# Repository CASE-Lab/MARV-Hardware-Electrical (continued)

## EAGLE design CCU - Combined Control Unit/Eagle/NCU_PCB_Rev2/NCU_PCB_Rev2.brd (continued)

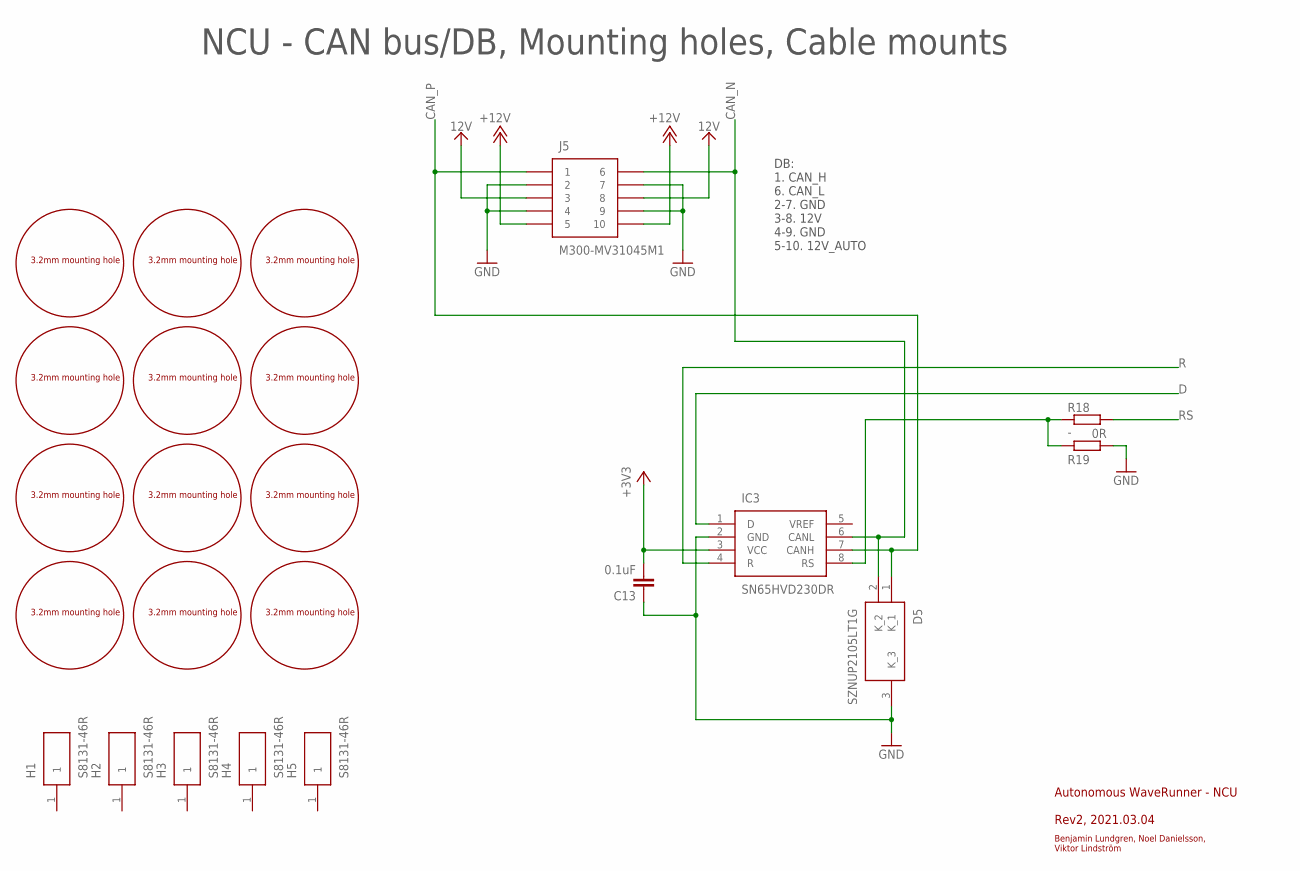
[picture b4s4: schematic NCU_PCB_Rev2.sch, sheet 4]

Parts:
C13: 0.1uF; C0603
D5: SZNUP2105LT1G; SOT96P237X111-3N
H1, H2, H3, H4, H5: S8131-46R; S813146R
HOLE5, HOLE6, HOLE7, HOLE8, HOLE9, HOLE10, HOLE11, HOLE12, HOLE13, HOLE14, HOLE15, HOLE16: M3_MOUNTING_HOLE
IC3: SN65HVD230DR; SOT127P600X175-8N
J5: M300-MV31045M1; M300MV31045M1
R18: -; R0603
R19: 0R; R0603

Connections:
12V: J5.3, J5.8; also elsewhere on the board
+3V3: C13.2, IC3.3 (VCC); also elsewhere on the board
+12V: J5.5, J5.10; also elsewhere on the board
CAN_N: D5.2 (K_2), IC3.6 (CANL), J5.6
CAN_P: D5.1 (K_1), IC3.7 (CANH), J5.1
D: IC3.1 (D); also elsewhere on the board
GND: C13.1, D5.3 (K_3), IC3.2 (GND), J5.2, J5.4, J5.7, J5.9, R19.1; also elsewhere on the board
unnamed: IC3.8 (RS), R18.1, R19.2
R: IC3.4 (R); also elsewhere on the board
RS: R18.2; also elsewhere on the board

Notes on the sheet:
Benjamin Lundgren, Noel Danielsson, Viktor Lindström
NCU - CAN bus/DB, Mounting holes, Cable mounts
DB: 1. CAN_H 6. CAN_L 2-7. GND 3-8. 12V 4-9. GND 5-10. 12V_AUTO
Autonomous WaveRunner - NCU
Rev2, 2021.03.04

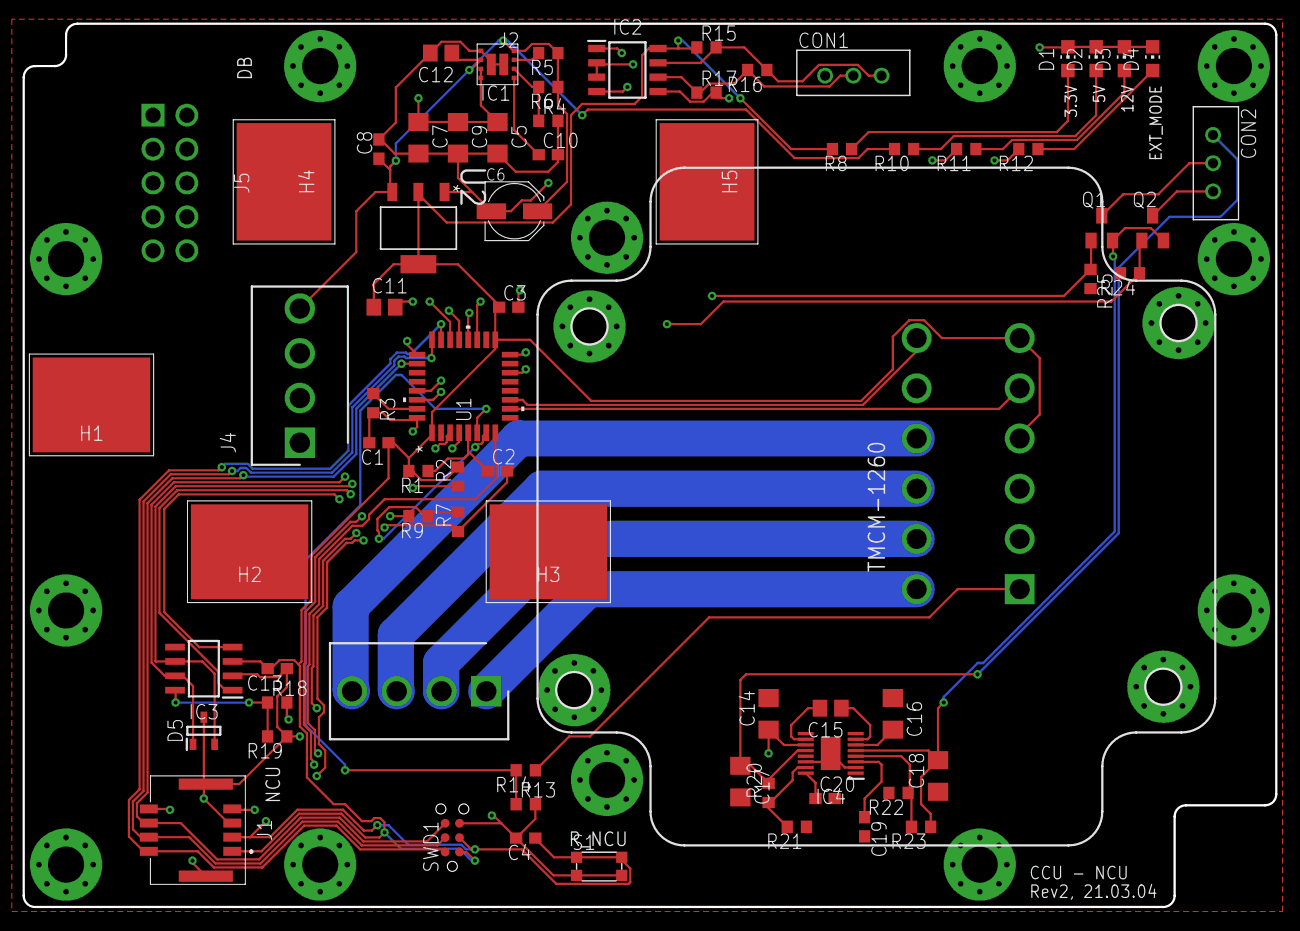
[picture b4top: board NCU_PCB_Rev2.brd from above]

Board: 4 copper layers, 110.9 x 78.2 mm, 89 parts (1 on the bottom side), 53 nets.

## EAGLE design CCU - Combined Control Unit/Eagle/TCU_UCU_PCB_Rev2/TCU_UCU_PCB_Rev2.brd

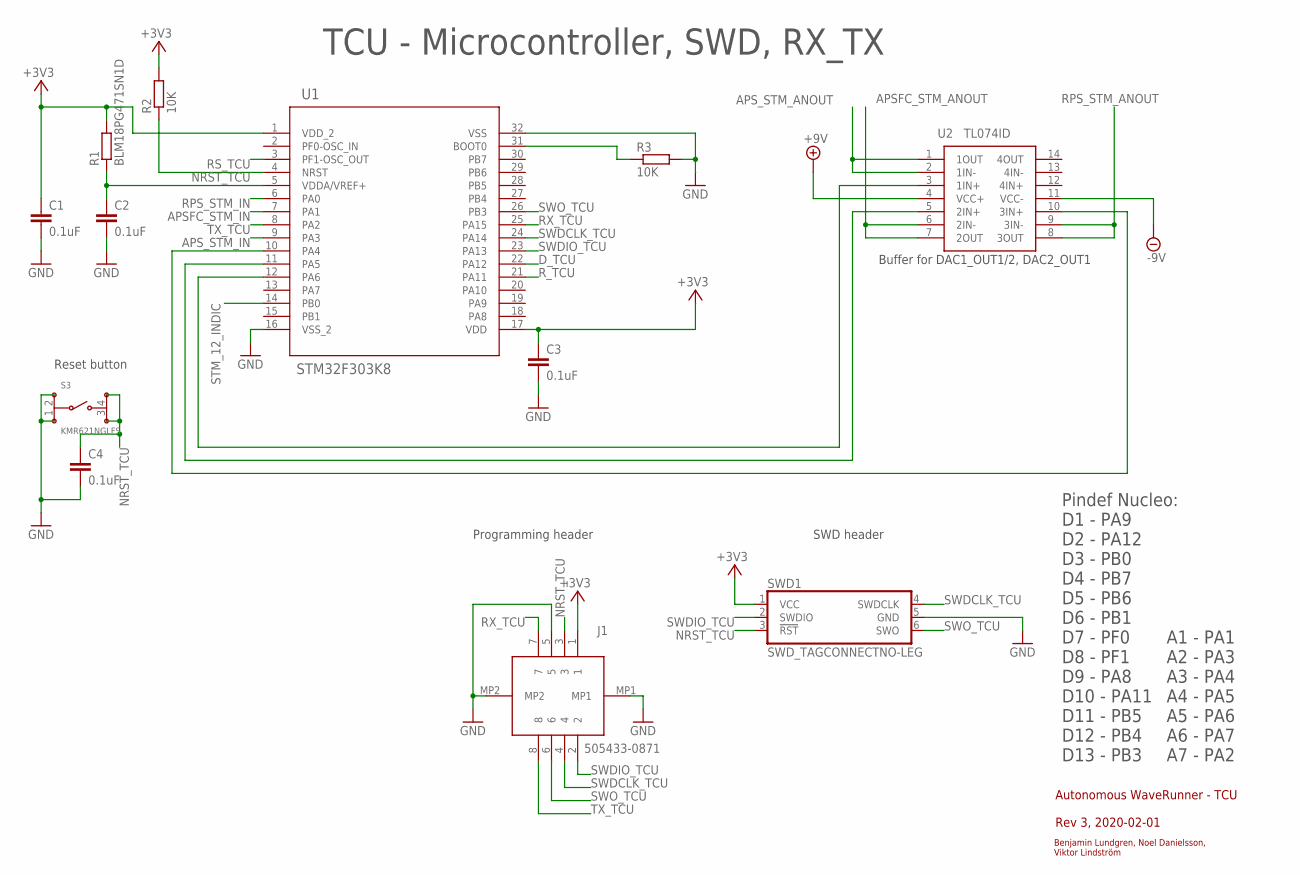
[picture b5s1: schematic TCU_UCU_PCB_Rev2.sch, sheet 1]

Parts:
C1, C2, C3, C4: 0.1uF; C0603
J1: 505433-0871; 5054330871
R1: BLM18PG471SN1D; R0603
R2, R3: 10K; R0603
S3: KMR621NGLFS
SWD1: SWD_TAGCONNECTNO-LEG; TC2030-IDC-NL
U1: STM32F303K8; LQFP-32
U2: TL074ID; SOIC127P600X175-14N

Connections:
+3V3: C1.1, C3.1, J1.1, R1.2, R2.2, SWD1.1 (VCC), U1.1 (VDD_2), U1.17 (VDD); also elsewhere on the board
+9V: U2.4 (VCC+); also elsewhere on the board
-9V: U2.11 (VCC-); also elsewhere on the board
APSFC_STM_ANOUT: U2.6 (2IN-), U2.7 (2OUT); also elsewhere on the board
APSFC_STM_IN: U1.7 (PA1); also elsewhere on the board
APS_STM_ANOUT: U2.1 (1OUT), U2.2 (1IN-); also elsewhere on the board
APS_STM_IN: U1.9 (PA3); also elsewhere on the board
D_TCU: U1.22 (PA12); also elsewhere on the board
GND: C1.2, C2.2, C3.2, C4.2, J1.5, J1.MP1, J1.MP2, R3.2, S3.1, S3.2, SWD1.5 (GND), U1.16 (VSS_2), U1.32 (VSS); also elsewhere on the board
unnamed: U1.11 (PA5), U2.5 (2IN+)
unnamed: U1.12 (PA6), U2.3 (1IN+)
unnamed: U1.10 (PA4), U2.10 (3IN+)
unnamed: C2.1, R1.1, U1.5 (VDDA/VREF+)
unnamed: R3.1, U1.31 (BOOT0)
NRST_TCU: C4.1, J1.3, R2.1, S3.3, S3.4, SWD1.3 (!RST), U1.4 (NRST)
RPS_STM_ANOUT: U2.8 (3OUT), U2.9 (3IN-); also elsewhere on the board
RPS_STM_IN: U1.6 (PA0); also elsewhere on the board
RS_TCU: U1.3 (PF1-OSC_OUT); also elsewhere on the board
RX_TCU: J1.7, U1.25 (PA15)
R_TCU: U1.21 (PA11); also elsewhere on the board
STM_12_INDIC: U1.14 (PB0); also elsewhere on the board
SWDCLK_TCU: J1.4, SWD1.4 (SWDCLK), U1.24 (PA14)
SWDIO_TCU: J1.2, SWD1.2 (SWDIO), U1.23 (PA13)
SWO_TCU: J1.6, SWD1.6 (SWO), U1.26 (PB3)
TX_TCU: J1.8, U1.8 (PA2)

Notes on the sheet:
Autonomous WaveRunner - TCU
Rev 3, 2020-02-01
Benjamin Lundgren, Noel Danielsson, Viktor Lindström
Buffer for DAC1_OUT1/2, DAC2_OUT1
Pindef Nucleo: D1 - PA9 D2 - PA12 D3 - PB0 D4 - PB7 D5 - PB6 D6 - PB1 D7 - PF0 D8 - PF1 D9 - PA8 D10 - PA11 D11 - PB5 D12 - PB4 D13 - PB3
A1 - PA1 A2 - PA3 A3 - PA4 A4 - PA5 A5 - PA6 A6 - PA7 A7 - PA2
TCU - Microcontroller, SWD, RX_TX
Programming header
SWD header
Reset button

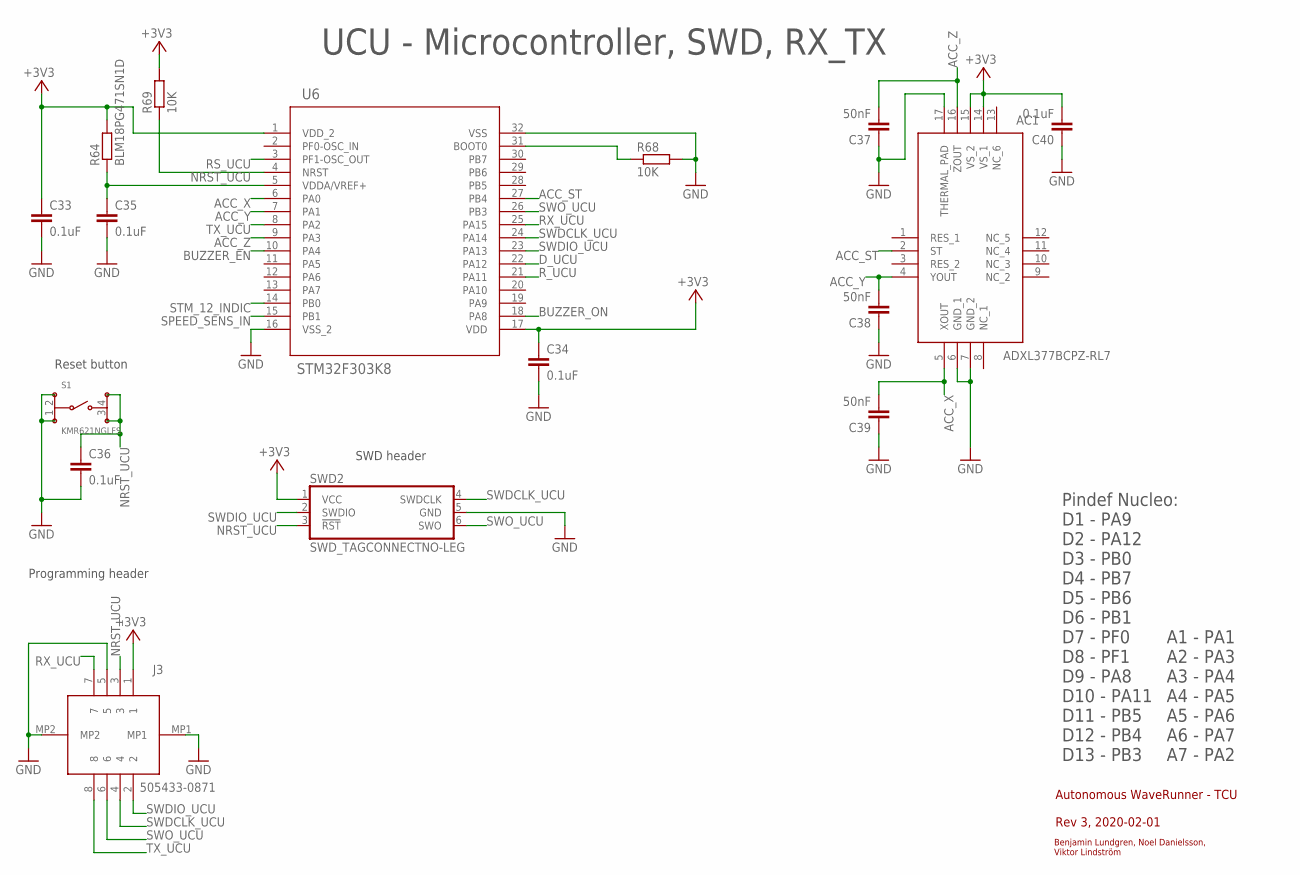
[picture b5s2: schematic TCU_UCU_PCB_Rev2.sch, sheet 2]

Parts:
AC1: ADXL377BCPZ-RL7; QFN50P300X300X150-17N
C33, C34, C35, C36, C40: 0.1uF; C0603
C37, C38, C39: 50nF; C0603
J3: 505433-0871; 5054330871
R64: BLM18PG471SN1D; R0603
R68, R69: 10K; R0603
S1: KMR621NGLFS
SWD2: SWD_TAGCONNECTNO-LEG; TC2030-IDC-NL
U6: STM32F303K8; LQFP-32

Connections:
+3V3: AC1.14 (VS_1), AC1.15 (VS_2), C33.1, C34.1, C40.2, J3.1, R64.2, R69.2, SWD2.1 (VCC), U6.1 (VDD_2), U6.17 (VDD); also elsewhere on the board
ACC_ST: AC1.2 (ST), U6.27 (PB4)
ACC_X: AC1.5 (XOUT), C39.2, U6.6 (PA0)
ACC_Y: AC1.4 (YOUT), C38.2, U6.7 (PA1)
ACC_Z: AC1.16 (ZOUT), C37.2, U6.9 (PA3)
BUZZER_EN: U6.10 (PA4); also elsewhere on the board
BUZZER_ON: U6.18 (PA8); also elsewhere on the board
D_UCU: U6.22 (PA12); also elsewhere on the board
GND: AC1.6 (GND_1), AC1.7 (GND_2), AC1.17 (THERMAL_PAD), C33.2, C34.2, C35.2, C36.2, C37.1, C38.1, C39.1, C40.1, J3.5, J3.MP1, J3.MP2, R68.2, S1.1, S1.2, SWD2.5 (GND), U6.16 (VSS_2), U6.32 (VSS); also elsewhere on the board
unnamed: C35.1, R64.1, U6.5 (VDDA/VREF+)
unnamed: R68.1, U6.31 (BOOT0)
NRST_UCU: C36.1, J3.3, R69.1, S1.3, S1.4, SWD2.3 (!RST), U6.4 (NRST)
RS_UCU: U6.3 (PF1-OSC_OUT); also elsewhere on the board
RX_UCU: J3.7, U6.25 (PA15)
R_UCU: U6.21 (PA11); also elsewhere on the board
SPEED_SENS_IN: U6.15 (PB1); also elsewhere on the board
STM_12_INDIC: U6.14 (PB0); also elsewhere on the board
SWDCLK_UCU: J3.4, SWD2.4 (SWDCLK), U6.24 (PA14)
SWDIO_UCU: J3.2, SWD2.2 (SWDIO), U6.23 (PA13)
SWO_UCU: J3.6, SWD2.6 (SWO), U6.26 (PB3)
TX_UCU: J3.8, U6.8 (PA2)

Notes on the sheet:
Autonomous WaveRunner - TCU
Rev 3, 2020-02-01
Benjamin Lundgren, Noel Danielsson, Viktor Lindström
UCU - Microcontroller, SWD, RX_TX
Programming header
SWD header
Reset button
Pindef Nucleo: D1 - PA9 D2 - PA12 D3 - PB0 D4 - PB7 D5 - PB6 D6 - PB1 D7 - PF0 D8 - PF1 D9 - PA8 D10 - PA11 D11 - PB5 D12 - PB4 D13 - PB3
A1 - PA1 A2 - PA3 A3 - PA4 A4 - PA5 A5 - PA6 A6 - PA7 A7 - PA2

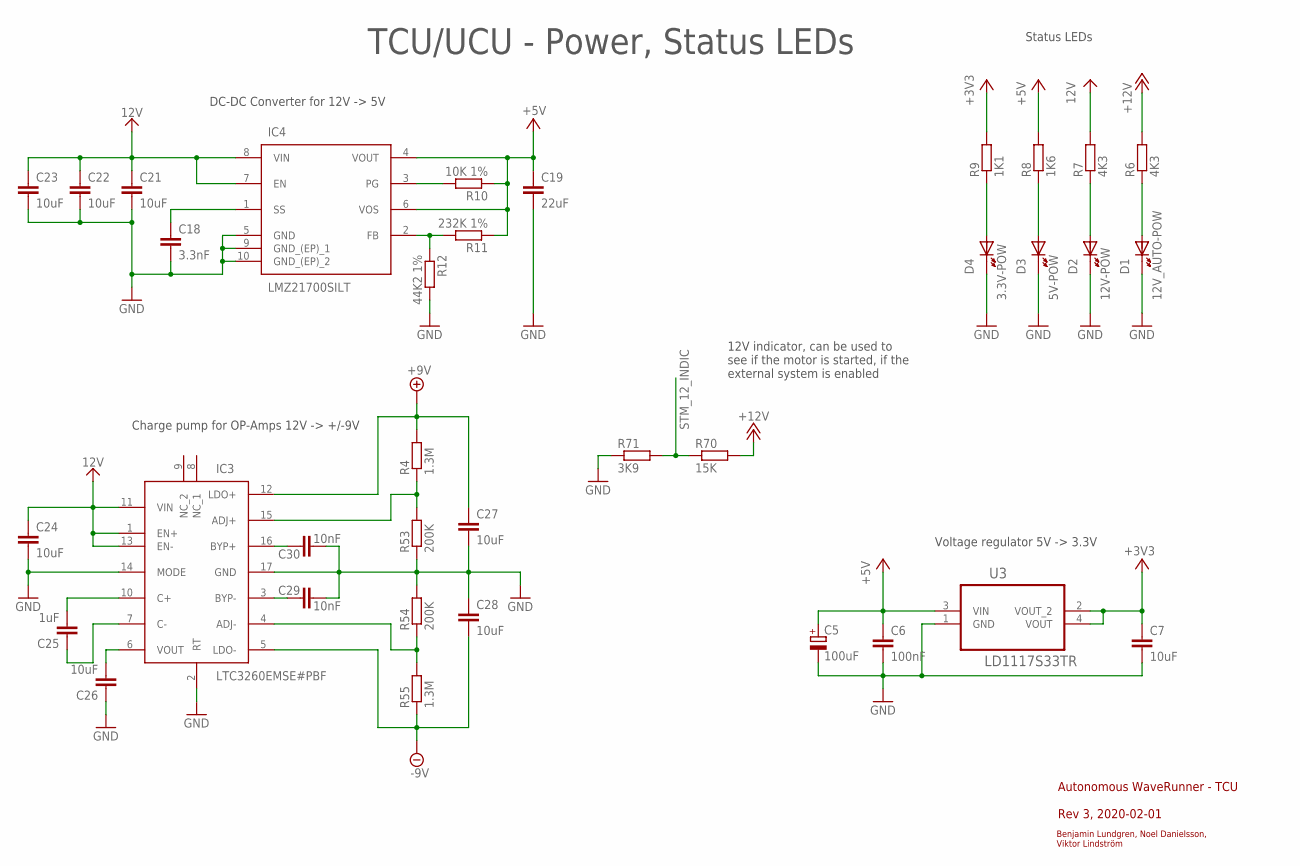
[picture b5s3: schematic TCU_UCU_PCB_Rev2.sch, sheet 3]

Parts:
C5: 100uF; PANASONIC_C
C6: 100nF; C0603
C7: 10uF; C0805
C18: 3.3nF; C0603
C19: 22uF; C0805
C21, C22, C23, C24, C26, C27, C28: 10uF; C1206
C25: 1uF; C0805
C29, C30: 10nF; C0603
D1: 12V_AUTO-POW; CHIP-LED0805
D2: 12V-POW; CHIP-LED0805
D3: 5V-POW; CHIP-LED0805
D4: 3.3V-POW; CHIP-LED0805
IC3: LTC3260EMSE#PBF; SOP50P490X110-17N
IC4: LMZ21700SILT; SIL0008E
R4, R55: 1.3M; R0603
R6, R7: 4K3; R0603
R8: 1K6; R0603
R9: 1K1; R0603
R10: 10K 1%; R0603
R11: 232K 1%; R0603
R12: 44K2 1%; R0603
R53, R54: 200K; R0603
R70: 15K; R0603
R71: 3K9; R0603
U3: LD1117S33TR; SOT230P700X180-4N

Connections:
12V: C21.1, C22.1, C23.1, C24.1, IC3.1 (EN+), IC3.11 (VIN), IC3.13 (EN-), IC4.7 (EN), IC4.8 (VIN), R7.2; also elsewhere on the board
+3V3: C7.1, R9.2, U3.2 (VOUT_2), U3.4 (VOUT); also elsewhere on the board
+5V: C5.+, C6.1, C19.1, IC4.4 (VOUT), IC4.6 (VOS), R8.2, R10.1, R11.1, U3.3 (VIN); also elsewhere on the board
+9V: C27.1, IC3.12 (LDO+), R4.2; also elsewhere on the board
+12V: R6.2, R70.2; also elsewhere on the board
-9V: C28.2, IC3.5 (LDO-), R55.1; also elsewhere on the board
GND: C5.-, C6.2, C7.2, C18.2, C19.2, C21.2, C22.2, C23.2, C24.2, C26.1, C27.2, C28.1, C29.2, C30.2, D1.C (K), D2.C (K), D3.C (K), D4.C (K), IC3.2 (RT), IC3.14 (MODE), IC3.17 (GND), IC4.5 (GND), IC4.9 (GND_(EP)_1), IC4.10 (GND_(EP)_2), R12.2, R53.1, R54.2, R71.1, U3.1 (GND); also elsewhere on the board
unnamed: C25.2, IC3.10 (C+)
unnamed: D1.A, R6.1
unnamed: IC4.2 (FB), R11.2, R12.1
unnamed: C18.1, IC4.1 (SS)
unnamed: D2.A, R7.1
unnamed: IC4.3 (PG), R10.2
unnamed: C25.1, IC3.7 (C-)
unnamed: C26.2, IC3.6 (VOUT)
unnamed: IC3.15 (ADJ+), R4.1, R53.2
unnamed: IC3.4 (ADJ-), R54.1, R55.2
unnamed: D3.A, R8.1
unnamed: C30.1, IC3.16 (BYP+)
unnamed: C29.1, IC3.3 (BYP-)
unnamed: D4.A, R9.1
STM_12_INDIC: R70.1, R71.2; also elsewhere on the board

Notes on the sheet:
Charge pump for OP-Amps 12V -> +/-9V
Status LEDs
Autonomous WaveRunner - TCU
Rev 3, 2020-02-01
Benjamin Lundgren, Noel Danielsson, Viktor Lindström
TCU/UCU - Power, Status LEDs
Voltage regulator 5V -> 3.3V
DC-DC Converter for 12V -> 5V
12V indicator, can be used to see if the motor is started, if the external system is enabled

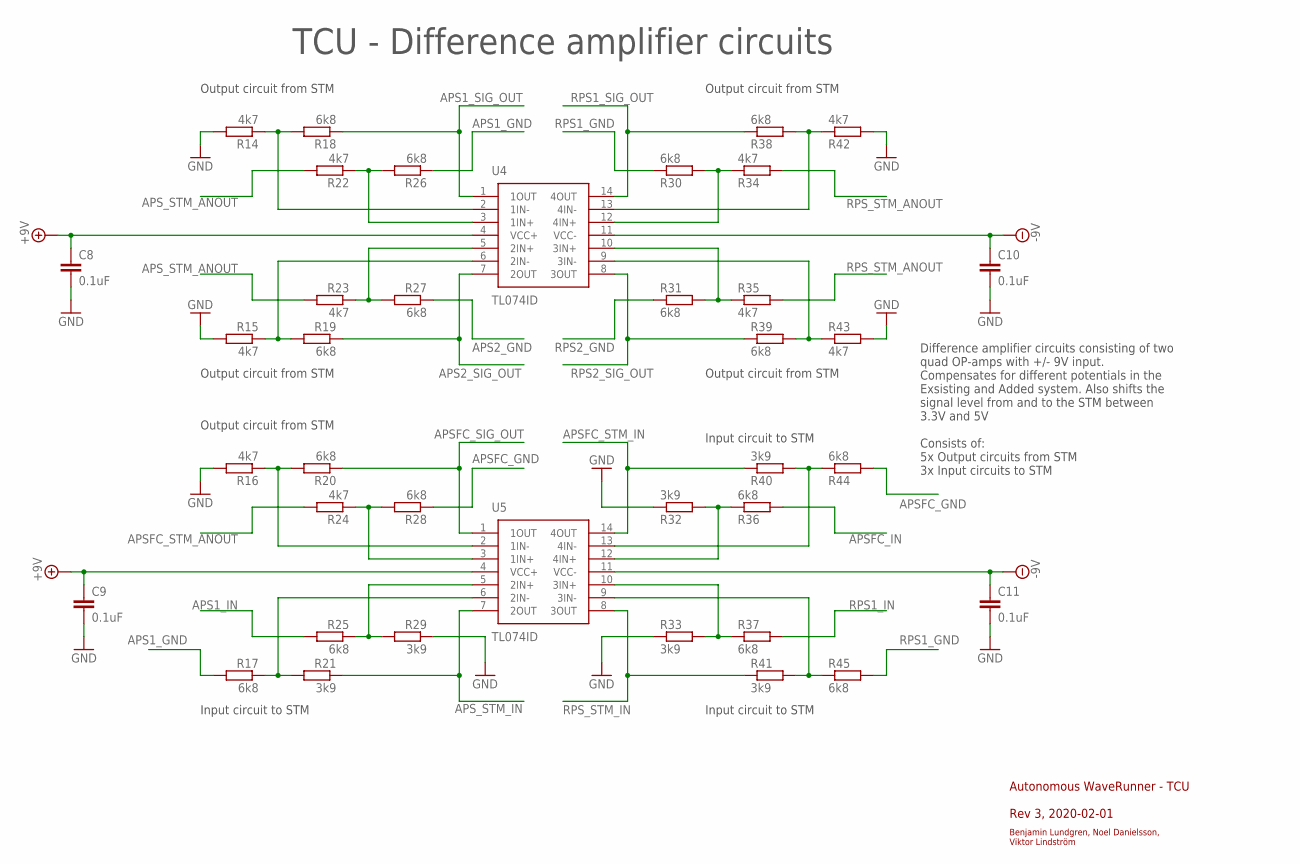
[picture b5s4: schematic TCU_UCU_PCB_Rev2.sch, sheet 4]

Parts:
C8, C9, C10, C11: 0.1uF; C0805
R14, R15, R16, R22, R23, R24, R34, R35, R42, R43: 4k7; R0603
R17, R18, R19, R20, R25, R26, R27, R28, R30, R31, R36, R37, R38, R39, R44, R45: 6k8; R0603
R21, R29, R32, R33, R40, R41: 3k9; R0603
U4, U5: TL074ID; SOIC127P600X175-14N

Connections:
+9V: C8.1, C9.1, U4.4 (VCC+), U5.4 (VCC+); also elsewhere on the board
-9V: C10.1, C11.1, U4.11 (VCC-), U5.11 (VCC-); also elsewhere on the board
APS1_GND: R17.2, R26.1; also elsewhere on the board
APS1_IN: R25.2; also elsewhere on the board
APS1_SIG_OUT: R18.1, U4.1 (1OUT); also elsewhere on the board
APS2_GND: R27.1; also elsewhere on the board
APS2_SIG_OUT: R19.1, U4.7 (2OUT); also elsewhere on the board
APSFC_GND: R28.1, R44.2; also elsewhere on the board
APSFC_IN: R36.2; also elsewhere on the board
APSFC_SIG_OUT: R20.1, U5.1 (1OUT); also elsewhere on the board
APSFC_STM_ANOUT: R24.2; also elsewhere on the board
APSFC_STM_IN: R40.1, U5.14 (4OUT); also elsewhere on the board
APS_STM_ANOUT: R22.2, R23.2; also elsewhere on the board
APS_STM_IN: R21.1, U5.7 (2OUT); also elsewhere on the board
GND: C8.2, C9.2, C10.2, C11.2, R14.2, R15.2, R16.2, R29.1, R32.1, R33.1, R42.2, R43.2; also elsewhere on the board
unnamed: R22.1, R26.2, U4.3 (1IN+)
unnamed: R14.1, R18.2, U4.2 (1IN-)
unnamed: R31.2, R35.1, U4.10 (3IN+)
unnamed: R39.2, R43.1, U4.9 (3IN-)
unnamed: R30.2, R34.1, U4.12 (4IN+)
unnamed: R38.2, R42.1, U4.13 (4IN-)
unnamed: R23.1, R27.2, U4.5 (2IN+)
unnamed: R15.1, R19.2, U4.6 (2IN-)
unnamed: R24.1, R28.2, U5.3 (1IN+)
unnamed: R16.1, R20.2, U5.2 (1IN-)
unnamed: R33.2, R37.1, U5.10 (3IN+)
unnamed: R41.2, R45.1, U5.9 (3IN-)
unnamed: R32.2, R36.1, U5.12 (4IN+)
unnamed: R40.2, R44.1, U5.13 (4IN-)
unnamed: R25.1, R29.2, U5.5 (2IN+)
unnamed: R17.1, R21.2, U5.6 (2IN-)
RPS1_GND: R30.1, R45.2; also elsewhere on the board
RPS1_IN: R37.2; also elsewhere on the board
RPS1_SIG_OUT: R38.1, U4.14 (4OUT); also elsewhere on the board
RPS2_GND: R31.1; also elsewhere on the board
RPS2_SIG_OUT: R39.1, U4.8 (3OUT); also elsewhere on the board
RPS_STM_ANOUT: R34.2, R35.2; also elsewhere on the board
RPS_STM_IN: R41.1, U5.8 (3OUT); also elsewhere on the board

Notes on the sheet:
Input circuit to STM
Output circuit from STM
Difference amplifier circuits consisting of two quad OP-amps with +/- 9V input. Compensates for different potentials in the Exsisting and Added system. Also shifts the signal level from and to the STM between 3.3V and 5V Consists of: 5x Output circuits from STM 3x Input circuits to STM
Autonomous WaveRunner - TCU
Rev 3, 2020-02-01
Benjamin Lundgren, Noel Danielsson, Viktor Lindström
TCU - Difference amplifier circuits

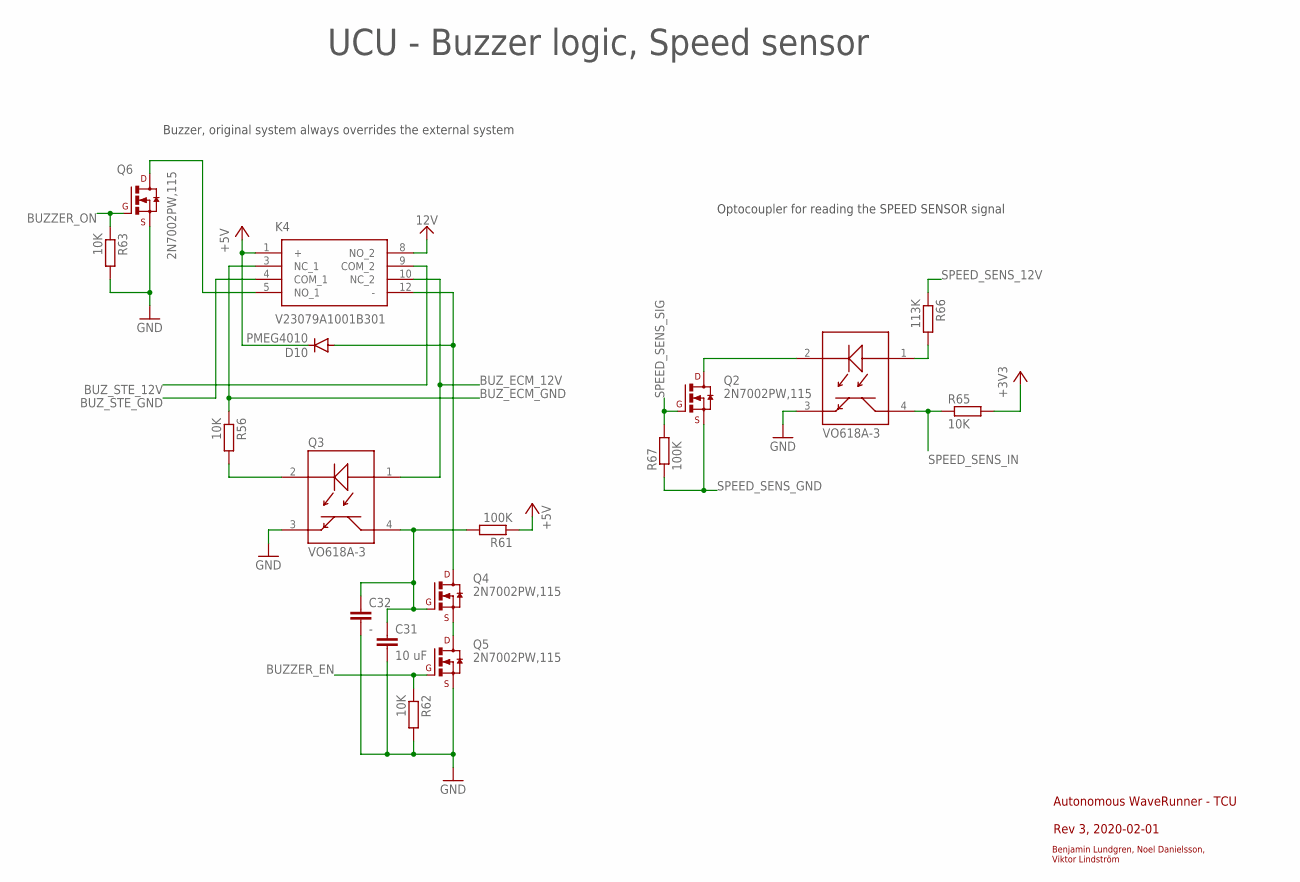
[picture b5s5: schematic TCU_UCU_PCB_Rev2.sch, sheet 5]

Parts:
C31: 10 uF; C0805
C32: -; C1206
D10: PMEG4010; SOD123
K4: V23079A1001B301; 413937885
Q2, Q4, Q5, Q6: 2N7002PW,115; SOT323
Q3, Q7: VO618A-3; DIL04-400
R56, R62, R63, R65: 10K; R0603
R61, R67: 100K; R0603
R66: 113K; R0603

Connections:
12V: K4.8 (NO_2); also elsewhere on the board
+3V3: R65.2; also elsewhere on the board
+5V: D10.C, K4.1 (+), R61.1; also elsewhere on the board
BUZZER_EN: Q5.1 (G), R62.1; also elsewhere on the board
BUZZER_ON: Q6.1 (G), R63.1; also elsewhere on the board
BUZ_ECM_12V: K4.10 (NC_2), Q3.1 (1A); also elsewhere on the board
BUZ_ECM_GND: K4.3 (NC_1), R56.1; also elsewhere on the board
BUZ_STE_12V: K4.9 (COM_2); also elsewhere on the board
BUZ_STE_GND: K4.4 (COM_1); also elsewhere on the board
GND: C31.2, C32.2, Q3.3 (3E), Q5.2 (S), Q6.2 (S), Q7.3 (3E), R62.2, R63.2; also elsewhere on the board
unnamed: Q2.3 (D), Q7.2 (2C)
unnamed: Q7.1 (1A), R66.2
unnamed: C31.1, C32.1, Q3.4 (4C), Q4.1 (G), R61.2
unnamed: D10.A, K4.12 (-), Q4.3 (D)
unnamed: Q4.2 (S), Q5.3 (D)
unnamed: K4.5 (NO_1), Q6.3 (D)
unnamed: Q3.2 (2C), R56.2
SPEED_SENS_12V: R66.1; also elsewhere on the board
SPEED_SENS_GND: Q2.2 (S), R67.1; also elsewhere on the board
SPEED_SENS_IN: Q7.4 (4C), R65.1; also elsewhere on the board
SPEED_SENS_SIG: Q2.1 (G), R67.2; also elsewhere on the board

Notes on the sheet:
Buzzer, original system always overrides the external system
Autonomous WaveRunner - TCU
Rev 3, 2020-02-01
Benjamin Lundgren, Noel Danielsson, Viktor Lindström
Optocoupler for reading the SPEED SENSOR signal
UCU - Buzzer logic, Speed sensor

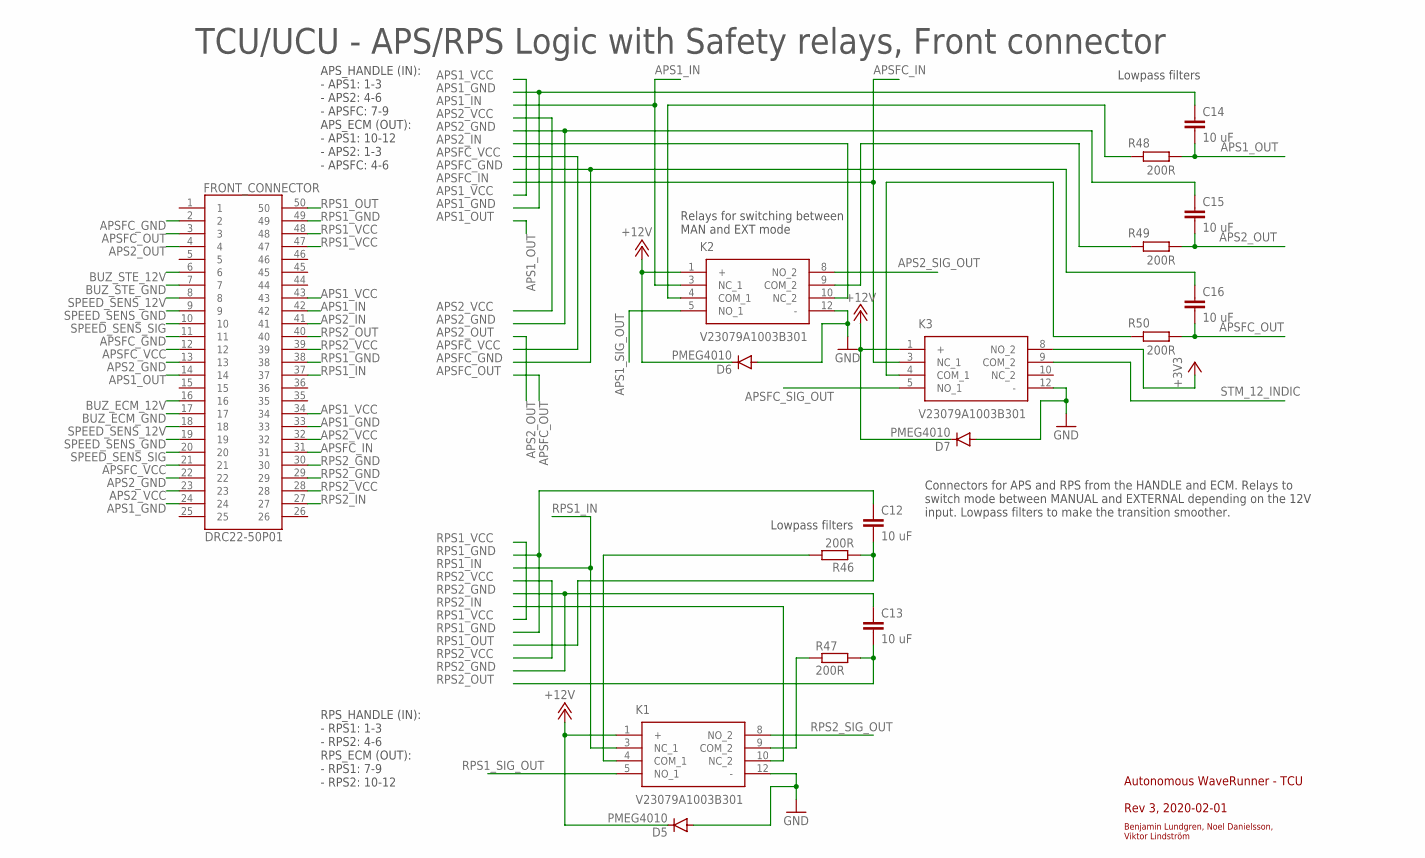
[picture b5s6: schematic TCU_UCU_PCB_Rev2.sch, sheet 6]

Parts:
C12, C13, C14, C15, C16: 10 uF; C0805
D5, D6, D7: PMEG4010; SOD123
FRONT_CONNECTOR: DRC22-50P01; TE_DRC22-50P01
K1, K2, K3: V23079A1003B301; 413937885
R46, R47, R48, R49, R50: 200R; R0603

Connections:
+3V3: K3.8 (NO_2); also elsewhere on the board
+12V: D5.C, D6.C, D7.C, K1.1 (+), K2.1 (+), K3.1 (+); also elsewhere on the board
APS1_GND: C14.1, FRONT_CONNECTOR.24, FRONT_CONNECTOR.33; also elsewhere on the board
APS1_IN: FRONT_CONNECTOR.42, K2.3 (NC_1); also elsewhere on the board
APS1_OUT: C14.2, FRONT_CONNECTOR.14, R48.1
APS1_SIG_OUT: K2.5 (NO_1); also elsewhere on the board
APS1_VCC: FRONT_CONNECTOR.34, FRONT_CONNECTOR.43
APS2_GND: C15.1, FRONT_CONNECTOR.13, FRONT_CONNECTOR.22; also elsewhere on the board
APS2_IN: FRONT_CONNECTOR.41, K2.10 (NC_2)
APS2_OUT: C15.2, FRONT_CONNECTOR.4, R49.1
APS2_SIG_OUT: K2.8 (NO_2); also elsewhere on the board
APS2_VCC: FRONT_CONNECTOR.23, FRONT_CONNECTOR.32
APSFC_GND: C16.1, FRONT_CONNECTOR.2, FRONT_CONNECTOR.11; also elsewhere on the board
APSFC_IN: FRONT_CONNECTOR.31, K3.3 (NC_1); also elsewhere on the board
APSFC_OUT: C16.2, FRONT_CONNECTOR.3, R50.1
APSFC_SIG_OUT: K3.5 (NO_1); also elsewhere on the board
APSFC_VCC: FRONT_CONNECTOR.12, FRONT_CONNECTOR.21
BUZ_ECM_12V: FRONT_CONNECTOR.16; also elsewhere on the board
BUZ_ECM_GND: FRONT_CONNECTOR.17; also elsewhere on the board
BUZ_STE_12V: FRONT_CONNECTOR.6; also elsewhere on the board
BUZ_STE_GND: FRONT_CONNECTOR.7; also elsewhere on the board
GND: D5.A, D6.A, D7.A, K1.12 (-), K2.12 (-), K3.12 (-); also elsewhere on the board
unnamed: K1.4 (COM_1), R46.2
unnamed: K1.9 (COM_2), R47.1
unnamed: K2.4 (COM_1), R48.2
unnamed: K2.9 (COM_2), R49.2
unnamed: K3.4 (COM_1), R50.2
RPS1_GND: C12.1, FRONT_CONNECTOR.38, FRONT_CONNECTOR.49; also elsewhere on the board
RPS1_IN: FRONT_CONNECTOR.37, K1.3 (NC_1); also elsewhere on the board
RPS1_OUT: C12.2, FRONT_CONNECTOR.50, R46.1
RPS1_SIG_OUT: K1.5 (NO_1); also elsewhere on the board
RPS1_VCC: FRONT_CONNECTOR.47, FRONT_CONNECTOR.48
RPS2_GND: C13.1, FRONT_CONNECTOR.29, FRONT_CONNECTOR.30; also elsewhere on the board
RPS2_IN: FRONT_CONNECTOR.27, K1.10 (NC_2)
RPS2_OUT: C13.2, FRONT_CONNECTOR.40, R47.2
RPS2_SIG_OUT: K1.8 (NO_2); also elsewhere on the board
RPS2_VCC: FRONT_CONNECTOR.28, FRONT_CONNECTOR.39
SPEED_SENS_12V: FRONT_CONNECTOR.8, FRONT_CONNECTOR.18; also elsewhere on the board
SPEED_SENS_GND: FRONT_CONNECTOR.9, FRONT_CONNECTOR.19; also elsewhere on the board
SPEED_SENS_SIG: FRONT_CONNECTOR.10, FRONT_CONNECTOR.20; also elsewhere on the board
STM_12_INDIC: K3.9 (COM_2); also elsewhere on the board

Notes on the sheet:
Lowpass filters
Relays for switching between MAN and EXT mode
Autonomous WaveRunner - TCU
Rev 3, 2020-02-01
Benjamin Lundgren, Noel Danielsson, Viktor Lindström
Connectors for APS and RPS from the HANDLE and ECM. Relays to switch mode between MANUAL and EXTERNAL depending on the 12V input. Lowpass filters to make the transition smoother.
RPS_HANDLE (IN): - RPS1: 1-3 - RPS2: 4-6 RPS_ECM (OUT): - RPS1: 7-9 - RPS2: 10-12
APS_HANDLE (IN): - APS1: 1-3 - APS2: 4-6 - APSFC: 7-9 APS_ECM (OUT): - APS1: 10-12 - APS2: 1-3 - APSFC: 4-6
TCU/UCU - APS/RPS Logic with Safety relays, Front connector

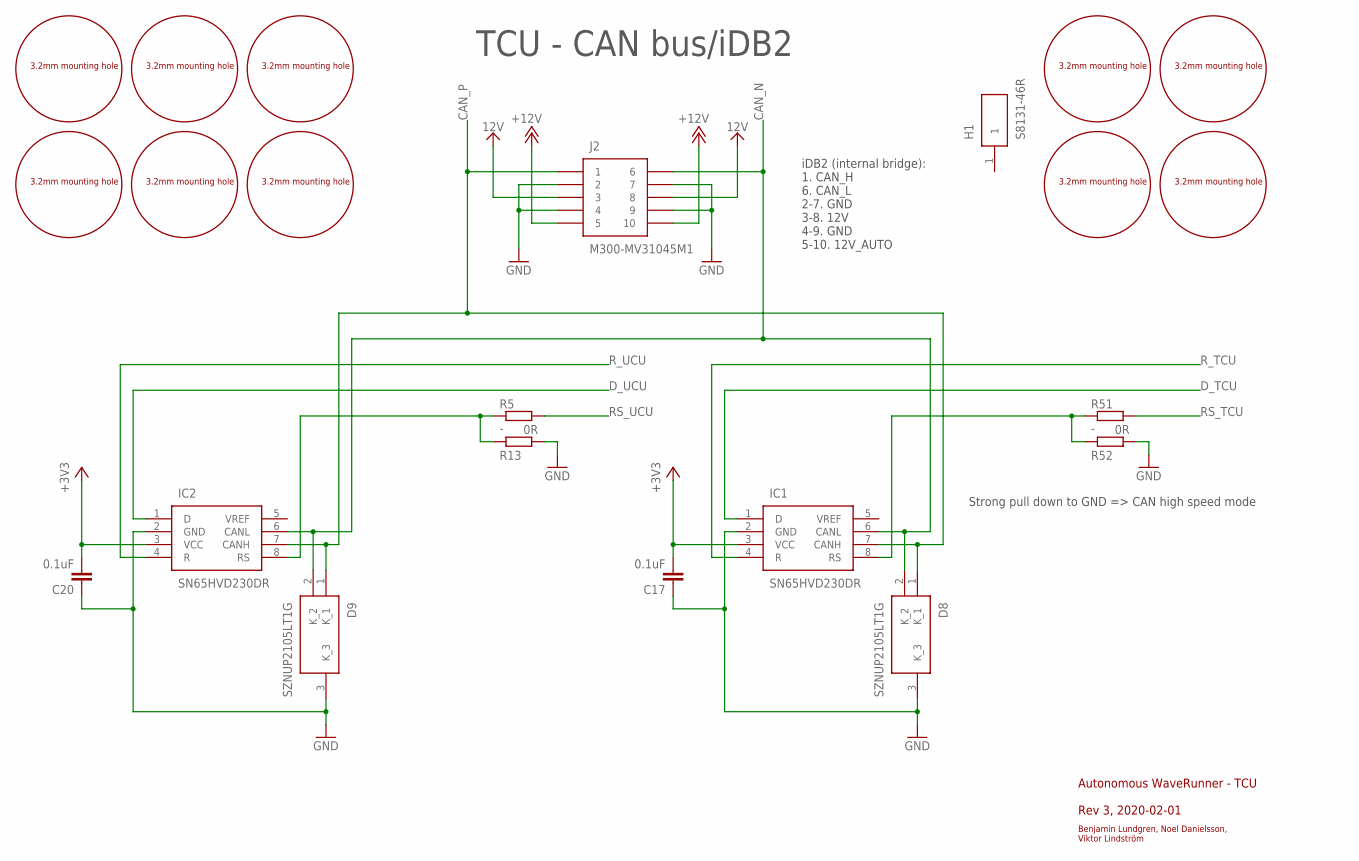
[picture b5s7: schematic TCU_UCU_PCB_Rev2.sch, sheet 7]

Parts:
C17, C20: 0.1uF; C0603
D8, D9: SZNUP2105LT1G; SOT96P237X111-3N
H1: S8131-46R; S813146R
IC1, IC2: SN65HVD230DR; SOT127P600X175-8N
J2: M300-MV31045M1; M300MV31045M1
R5, R51: -; R0603
R13, R52: 0R; R0603
U$1, U$2, U$3, U$4, U$5, U$6, U$7, U$8, U$9, U$10: M3_MOUNTING_HOLE

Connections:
12V: J2.3, J2.8; also elsewhere on the board
+3V3: C17.2, C20.2, IC1.3 (VCC), IC2.3 (VCC); also elsewhere on the board
+12V: J2.5, J2.10; also elsewhere on the board
CAN_N: D8.2 (K_2), D9.2 (K_2), IC1.6 (CANL), IC2.6 (CANL), J2.6
CAN_P: D8.1 (K_1), D9.1 (K_1), IC1.7 (CANH), IC2.7 (CANH), J2.1
D_TCU: IC1.1 (D); also elsewhere on the board
D_UCU: IC2.1 (D); also elsewhere on the board
GND: C17.1, C20.1, D8.3 (K_3), D9.3 (K_3), IC1.2 (GND), IC2.2 (GND), J2.2, J2.4, J2.7, J2.9, R13.1, R52.1; also elsewhere on the board
unnamed: IC1.8 (RS), R51.1, R52.2
unnamed: IC2.8 (RS), R5.1, R13.2
RS_TCU: R51.2; also elsewhere on the board
RS_UCU: R5.2; also elsewhere on the board
R_TCU: IC1.4 (R); also elsewhere on the board
R_UCU: IC2.4 (R); also elsewhere on the board

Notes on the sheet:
Autonomous WaveRunner - TCU
Rev 3, 2020-02-01
Benjamin Lundgren, Noel Danielsson, Viktor Lindström
TCU - CAN bus/iDB2
iDB2 (internal bridge): 1. CAN_H 6. CAN_L 2-7. GND 3-8. 12V 4-9. GND 5-10. 12V_AUTO
Strong pull down to GND => CAN high speed mode

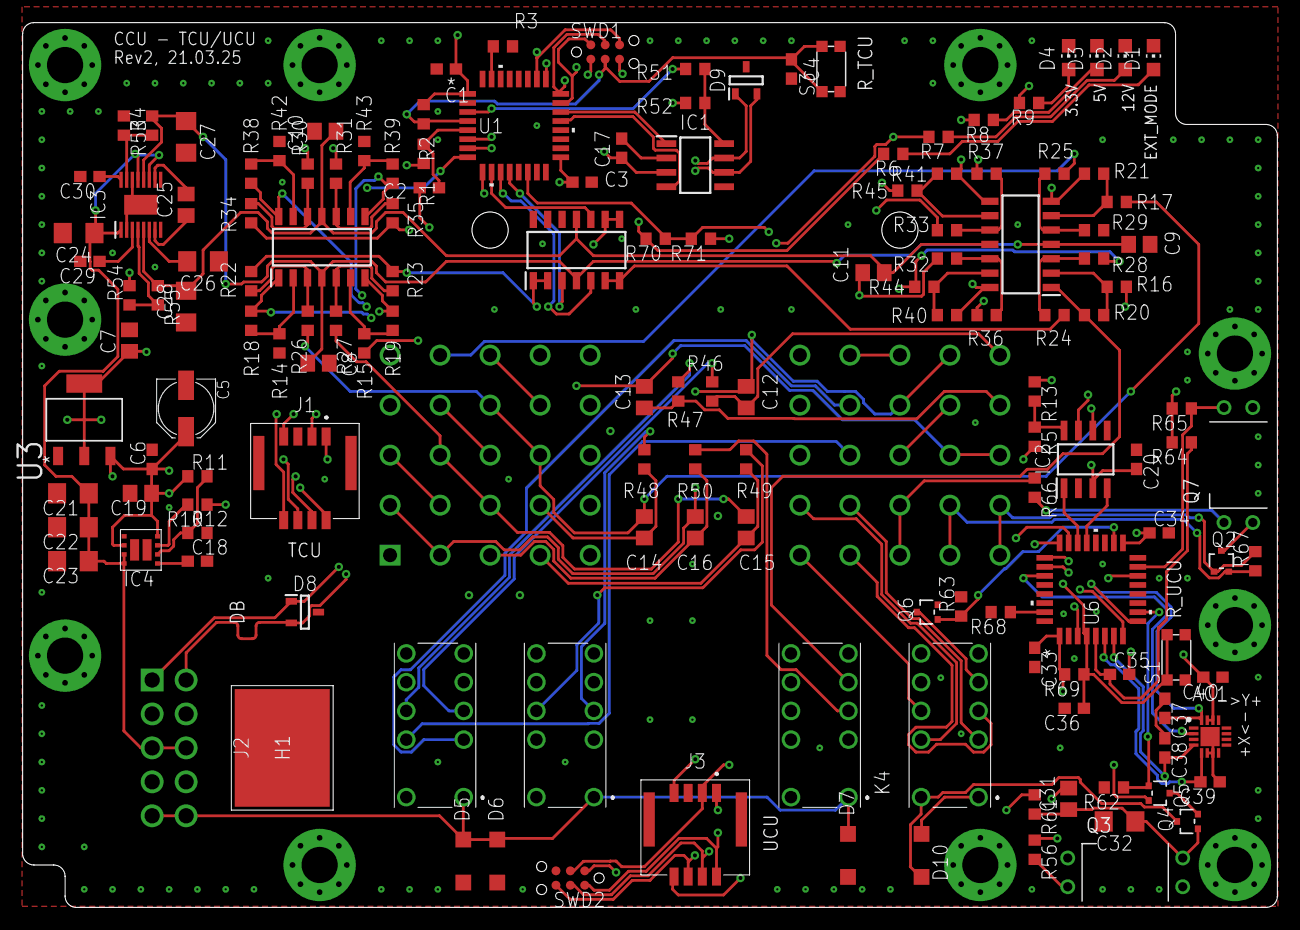
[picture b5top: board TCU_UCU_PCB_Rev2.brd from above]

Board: 4 copper layers, 110.9 x 78.2 mm, 157 parts (1 on the bottom side), 124 nets.
